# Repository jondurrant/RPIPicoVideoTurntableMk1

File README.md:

# RPIPicoVideoTurntableMk1
RPI Pico Video Turntable Mk1. Vidio on this project is available at [https://youtube.com/@drjonea](https://youtube.com/@drjonea).

Still images are boring and when they are PCB or breadboard sometimes dificult to understand from one angle. This project is a controlled turntable for small scale video work on my projects. 

## Features

**Lighting** Uses a strip of WS2812B LEDs to illuminate the photo area. Controlled in terms of Hue, Saturation and Value.

**Calibration** Self calibrating turn table driven by a 28BYJ-48 stepper motor

**Menu** Simple menu displayed on a OLED display and controled through a Rotary Encoder.

**Sequence** Switch 1 moves the turntable to start possition by shortest route and then moves to the end possition in the direction and speed set in the configuration. Good for setup and repeat takes of the same shot

**Stop** Switch 2 stops the turntable.

**Continuous Rotation** Switch 3 provides continuous rotation and the currently configured speed. Short press is clockwise, long press is counterclockwise.

**Reset** Switch 4 resets the turntable

**Pico Reset** Switch 5 is the Pico Reset.

## Schematic and PCB

KiCad files have been included in the Schematic folder.

PDF version of the schematic is also included.

Gerb files are included in the PCB folder 

## 3D Models

OpenSCAD project is in the folder 3DModels. You will need two supporting libraries.

Download [gears.scad](https://www.thingiverse.com/thing:4194148/files)

Download [stepper.scad](https://www.thingiverse.com/thing:4031757/files)

## Libraries

+ [FreeRTOS Kernel](https://github.com/FreeRTOS/FreeRTOS-Kernel)
+ [PicoLED](https://github.com/ForsakenNGS/PicoLED)
+ [pico-ssd1306](https://github.com/daschr/pico-ssd1306)

## Clone and Build

```
git clone --recurse-submodules https://github.com/jondurrant/RPIPicoVideoTurntableMk1
cd RPIPicoVideoTurntableMk1
mkdir build
cd build
cmake ..
make
```

## Links

+ Further YouTube projects on my channel [YouTube @DrJonEa](https://youtube.com/@drjonea).
+ Blogs at [DrJonEa.co.uk](https://drjonea.co.uk/IoT)
+ RPI Pico Courses at [Udemy @DrJonEa](https://drjonea.co.uk/training/)

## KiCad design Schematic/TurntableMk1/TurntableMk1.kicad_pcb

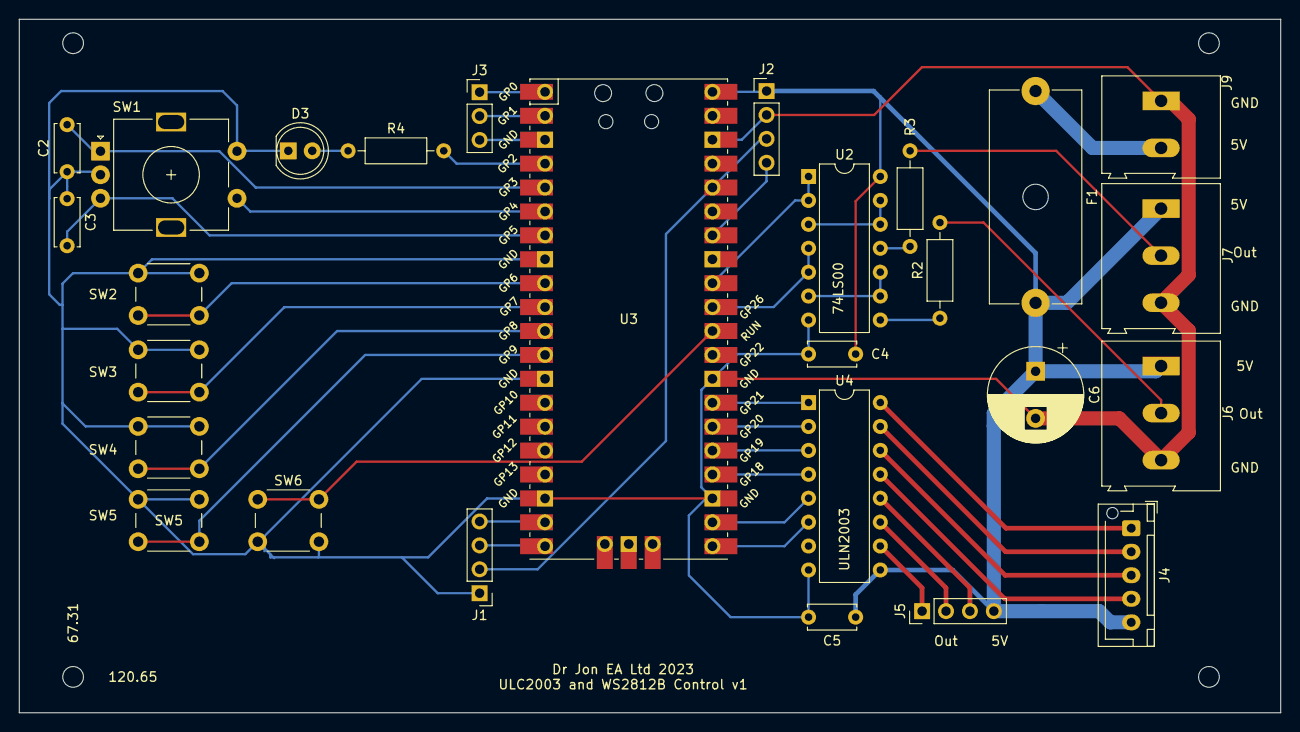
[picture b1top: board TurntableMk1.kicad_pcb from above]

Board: 2 copper layers, 134.0 x 73.7 mm, 27 parts (0 on the bottom side), 41 nets.

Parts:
C2, C3: 10nF; C_Disc_D5.0mm_W2.5mm_P5.00mm
C4, C5: 100nf; C_Disc_D5.0mm_W2.5mm_P5.00mm
C6: 1000uF; CP_Radial_D10.0mm_P5.00mm
D3: LED; LED_D5.0mm
F1: Fuse 5A; Fuseholder_Cylinder-5x20mm_Schurter_0031_8201_Horizontal_Op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
J1, J2, J5: Conn_01x04_Male; PinHeader_1x04_P2.54mm_Vertical
J3: Uart; PinHeader_1x03_P2.54mm_Vertical
J4: Conn_01x05; JST_XH_B5B-XH-AM_1x05_P2.50mm_Vertical
J6, J7: Screw_Terminal_01x03; TerminalBlock_Altech_AK300-3_P5.00mm
J9: Screw_Terminal_01x02; TerminalBlock_Altech_AK300-2_P5.00mm
R2, R3: 330R; R_Axial_DIN0207_L6.3mm_D2.5mm_P10.16mm_Horizontal
R4: 75R; R_Axial_DIN0207_L6.3mm_D2.5mm_P10.16mm_Horizontal
SW1: RotaryEncoder_Switch; RotaryEncoder_Alps_EC11E-Switch_Vertical_H20mm
SW2, SW3, SW4, SW5, SW6: SW_Push; SW_PUSH_6mm
U2: 74LS00; DIP-14_W7.62mm
U3: Pico; RPi_Pico_SMD_TH
U4: ULN2003; DIP-16_W7.62mm

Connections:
+3.3V: J1.2, J2.3, U3.36 (3V3)
+5V: C4.1, C5.1, C6.1, F1.2, J2.1, J4.5, J5.4, J6.1, J7.1, U2.14 (VCC), U3.40 (VBUS), U4.9 (COM)
GND: C2.1, C3.1, C4.2, C5.2, C6.2, D3.1 (K), J1.1, J2.2, J6.3, J7.3, J9.1, SW1.C, SW1.S2, SW2.1, SW3.1, SW4.1, SW5.1, SW6.2, U2.7 (GND), U3.8 (GND), U3.13 (GND), U3.18 (GND), U3.23 (GND), U3.28 (GND), U3.38 (GND), U4.8 (GND)
unnamed: C2.2, SW1.A, U3.5 (GPIO3)
unnamed: C3.2, SW1.B, U3.7 (GPIO5)
unnamed: J6.2, R2.2
unnamed: J7.2, R3.2
unnamed: D3.2 (A), R4.1
unnamed: F1.1, J9.2
unnamed: J1.3, U3.20 (GPIO15)
unnamed: J3.1 (TX), U3.1 (GPIO0)
unnamed: J3.2 (RX), U3.2 (GPIO1)
unnamed: J3.3 (GND), U3.3 (GND)
unnamed: J4.1, U4.16 (O1)
unnamed: J4.2, U4.15 (O2)
unnamed: J4.3, U4.14 (O3)
unnamed: J4.4, U4.13 (O4)
unnamed: J5.1, U4.10 (O7)
unnamed: J5.2, U4.11 (O6)
unnamed: J5.3, U4.12 (O5)
unnamed: R2.1, U2.8
unnamed: R3.1, U2.11
unnamed: R4.2, U3.4 (GPIO2)
unnamed: SW1.S1, U3.6 (GPIO4)
unnamed: SW2.2, U3.9 (GPIO6)
unnamed: SW3.2, U3.10 (GPIO7)
unnamed: SW4.2, U3.11 (GPIO8)
unnamed: SW5.2, U3.12 (GPIO9)
unnamed: SW6.1, U3.30 (RUN)
unnamed: U2.1, U2.2, U3.32 (GPIO27_ADC1)
unnamed: U2.4, U2.5, U3.31 (GPIO26_ADC0)
unnamed: U2.6, U2.9, U2.10
unnamed: U2.3, U2.12, U2.13
unnamed: J1.4, U3.19 (GPIO14)
unnamed: U3.21 (GPIO16), U4.6 (I6)
unnamed: U3.22 (GPIO17), U4.5 (I5)
unnamed: U3.24 (GPIO18), U4.4 (I4)
unnamed: U3.25 (GPIO19), U4.3 (I3)
unnamed: U3.26 (GPIO20), U4.2 (I2)
unnamed: U3.27 (GPIO21), U4.1 (I1)
unnamed: J2.4, U3.34 (GPIO28_ADC2)

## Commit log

2023-02-25 Shared version
